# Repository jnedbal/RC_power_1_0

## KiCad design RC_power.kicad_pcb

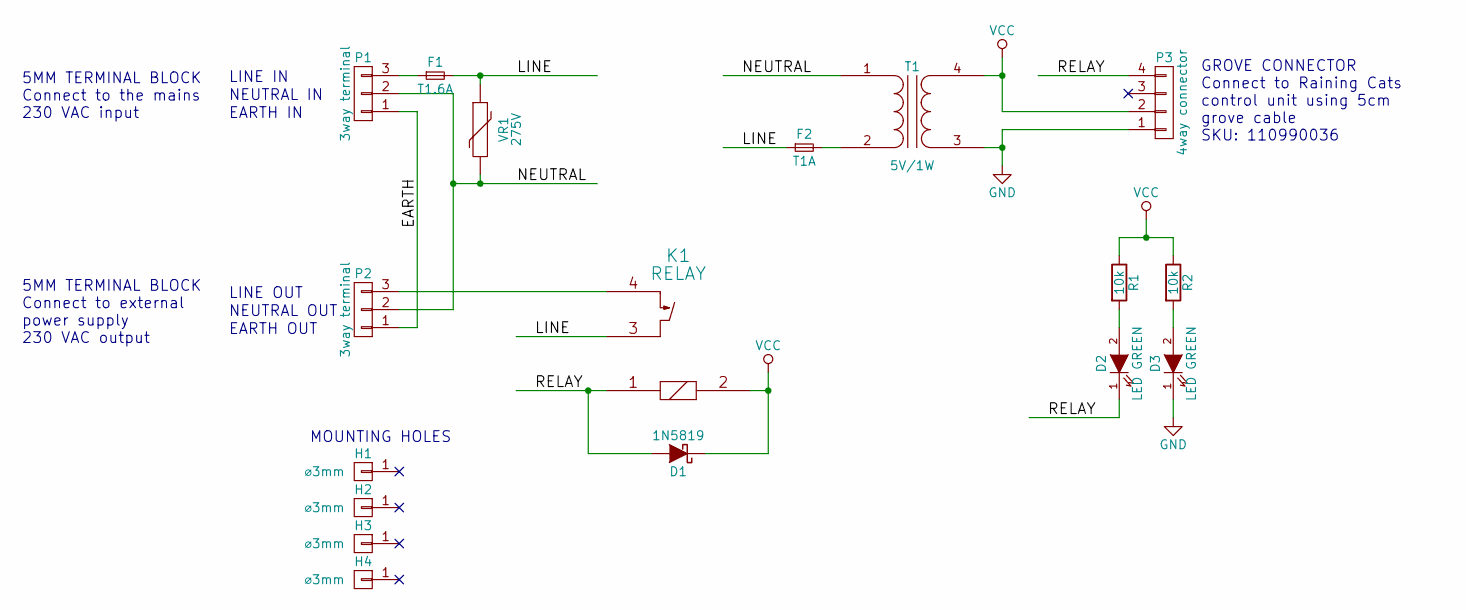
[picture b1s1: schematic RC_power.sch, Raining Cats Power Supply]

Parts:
D1: 1N5819; SOD-123; Part Number 1N5819HW-7-F
D2, D3: LED GREEN; LED_0603; Part Number 19-217-G7C-AN1P2-3T
F1: T1.6A; Fuseholder5x20_horiz_open_Schurter_0031_8201; Part Number 0031.8201
F2: T1A; Fuseholder5x20_horiz_open_Schurter_0031_8201; Part Number 0031.8201
H1, H2, H3, H4: ⌀3mm; MountingHole_3.2mm_M3
K1: RELAY; PCNrelay; Part Number PCN-105D3MHZ
P1, P2: 3way terminal; TerminalBlock_Pheonix_MKDS1.5-3pol; Part Number 22-23-2031
P3: 4way connector; JST_PH_04way_vert; Part Number 1125S-4P
R1, R2: 10k; R_0603; Part Number RC0603FR-0710KL
T1: 5V/1W; RAC01-02; Part Number RAC01-05SC
VR1: 275V; RV_Disc_D15.5_W5_P7.5; Part Number B72214S0271K101

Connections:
/EARTH: P1.1, P2.1
/LINE: F1.2, F2.1, K1.3, VR1.1
/NEUTRAL: P1.2, P2.2, T1.1 (AA), VR1.2
/RELAY: D1.2 (A), D2.1 (K), K1.1, P3.4
GND: D3.1 (K), P3.1, T1.3 (SA)
unnamed: D2.2 (A), R1.2
unnamed: D3.2 (A), R2.2
unnamed: F1.1, P1.3
unnamed: F2.2, T1.2 (AB)
unnamed: K1.4, P2.3
VCC: D1.1 (K), K1.2, P3.2, R1.1, R2.1, T1.4 (SB)

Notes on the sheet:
LINE IN
NEUTRAL IN
EARTH IN
LINE OUT
NEUTRAL OUT
EARTH OUT
MOUNTING HOLES
GROVE CONNECTOR Connect to Raining Cats control unit using 5cm grove cable SKU: 110990036
5MM TERMINAL BLOCK Connect to the mains 230 VAC input
5MM TERMINAL BLOCK Connect to external power supply 230 VAC output

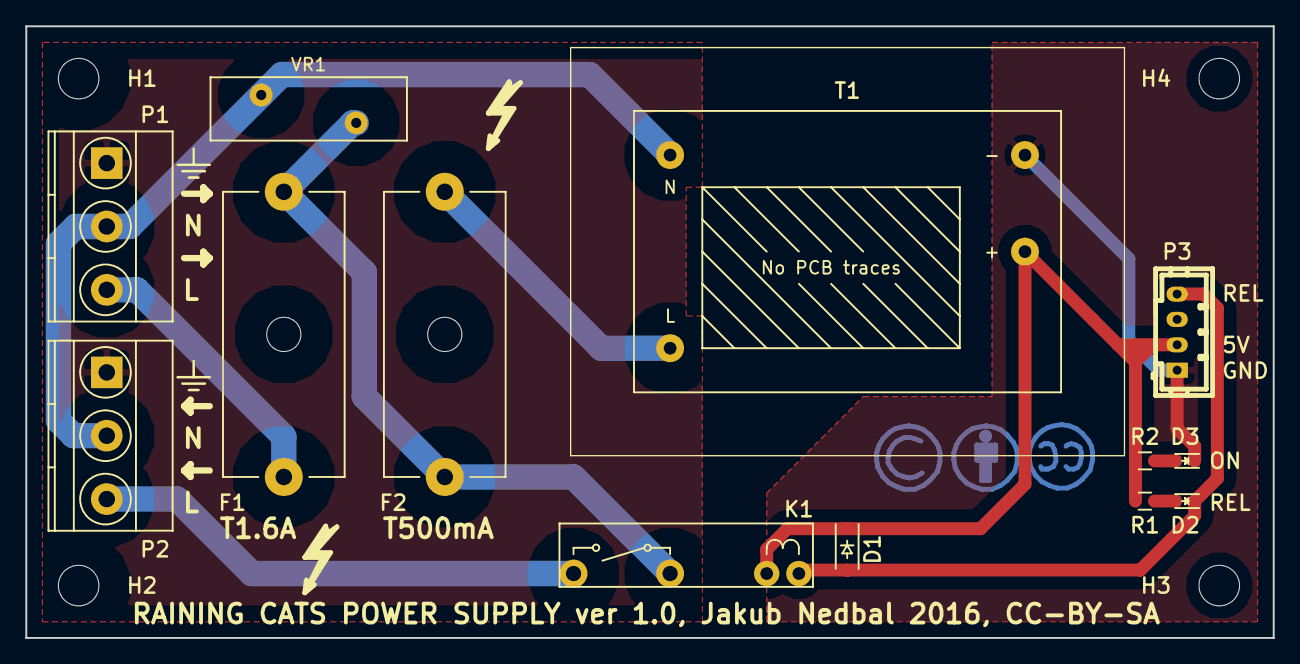
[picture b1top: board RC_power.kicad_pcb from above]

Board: 2 copper layers, 98.4 x 48.3 mm, 17 parts (0 on the bottom side), 11 nets.

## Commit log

2016-09-25 Added .gitignore to ignore zip files and ods files
2016-09-25 Used protel extensions on gerber files
2016-10-07 Final production board
2016-10-07 Added Seeed component list

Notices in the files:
RC_power.kicad_pcb:
License: CC-BY-SA
RAINING CATS POWER SUPPLY ver 1.0, Jakub Nedbal 2016, CC-BY-SA
